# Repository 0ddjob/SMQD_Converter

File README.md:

The Sinclair ZX Spectrum clones that came out of the Soviet/post-Soviet regions tended to use 14MHz crystals as these could be used to generate an easy 7MHz and 3.5MHz signal.<br>

These 14MHz crystals are not easy to obtain now (obsolete) in their original package type, but are available as surface mount devices.<br>

So I thought I might see if it's possible to use them to replace suspect 14MHz crystals in these Eastern Bloc clones.<br>

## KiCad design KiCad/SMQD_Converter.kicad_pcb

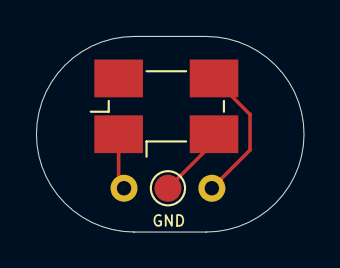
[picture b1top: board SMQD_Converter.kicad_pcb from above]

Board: 2 copper layers, 14.9 x 10.9 mm, 3 parts (0 on the bottom side), 3 nets.

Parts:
J1: XTAL; Crystal_HC49-U_Vertical
J2: GND; TestPoint_Pad_D1.5mm
Y1: Crystal_GND24; Crystal_SMD_0603-4Pin_6.0x3.5mm_HandSoldering

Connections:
GND: J2.1, Y1.2, Y1.4
XTAL1: J1.1, Y1.1
XTAL2: J1.2, Y1.3

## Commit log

2025-05-14 Initial design
2025-05-15 Sent for test fabrication
